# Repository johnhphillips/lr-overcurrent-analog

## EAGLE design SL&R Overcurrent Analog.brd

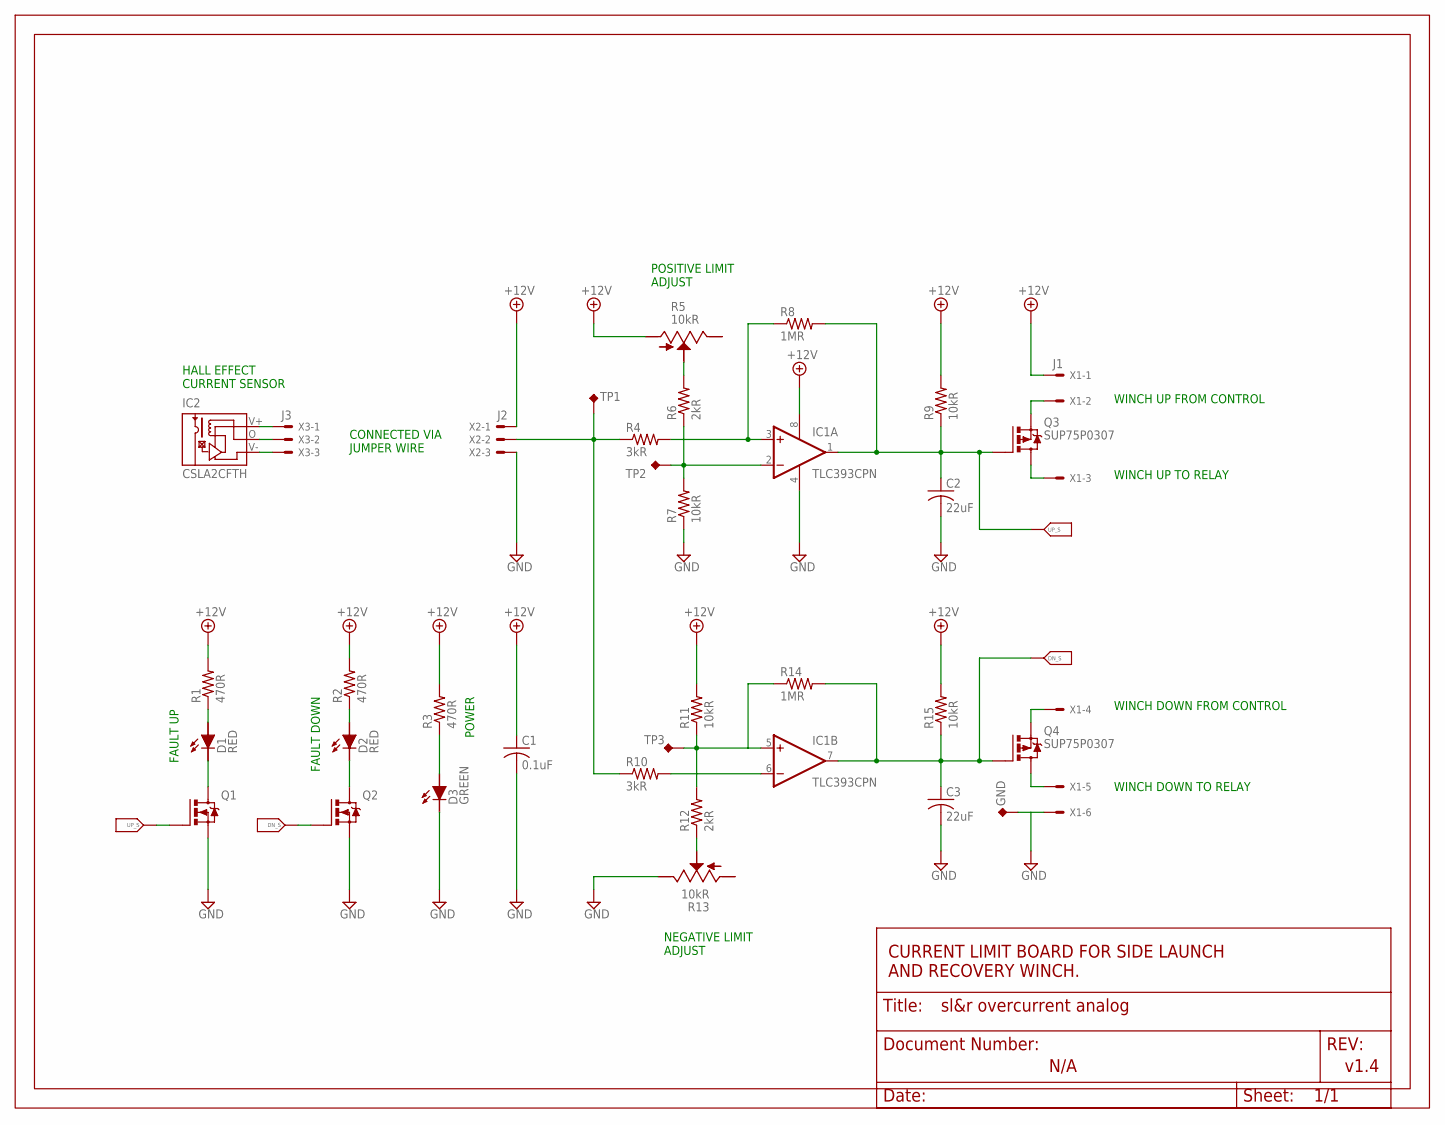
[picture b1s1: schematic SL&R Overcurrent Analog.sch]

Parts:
C1: 0.1uF; C050-024X044
C2, C3: 22uF; C025-050X050
D1, D2: RED; LED5MM
D3: GREEN; LED5MM
FRAME1: FRAME_A_L
GND: TEST_POINT; TESTLOOP
IC1: TLC393CPN; DIL08
IC2: CSLA2CFTH; CSLA2CF
Q1, Q2: 2N7000; TO92-
Q3, Q4: SUP75P0307; TO220BV
R1, R2, R3: 470R; 0204/7
R4, R10: 3kR; 0204/7
R5, R13: 10kR; RTRIM3296W
R6, R12: 2kR; 0204/7
R7, R9, R11, R15: 10kR; 0204/7
R8, R14: 1MR; 0204/7
TP1, TP2, TP3: TEST_POINT; TESTLOOP
U$1: DOCFIELD
X1: J1; 22-23-2061
X2: J2; 22-23-2031
X3: J3; 22-23-2031

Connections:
+12V: C1.1, IC1.8 (V+), R1.2, R2.2, R3.2, R5.3, R9.2, R11.2, R15.2, X1.1, X2.1
GND: C1.2, C2.2, C3.2, D3.K (C), GND.P$1, IC1.4 (V-), Q1.3 (S), Q2.3 (S), R7.1, R13.1, X1.6, X2.3
unnamed: IC1.3 (+IN), R4.2, R8.1
unnamed: IC1.2 (-IN), R6.1, R7.2, TP2.P$1
unnamed: D1.A, R1.1
unnamed: IC1.6 (-IN), R10.2
unnamed: IC1.5 (+IN), R11.1, R12.2, R14.1, TP3.P$1
unnamed: C2.1, IC1.1 (OUT), Q1.2 (G), Q3.G, R8.2, R9.1
unnamed: C3.1, IC1.7 (OUT), Q2.2 (G), Q4.G, R14.2, R15.1
unnamed: Q3.S, X1.2
unnamed: Q3.D, X1.3
unnamed: Q4.S, X1.4
unnamed: Q4.D, X1.5
unnamed: IC2.V+, X3.1
unnamed: IC2.V-, X3.3
unnamed: IC2.O (M), X3.2
unnamed: R4.1, R10.1, TP1.P$1, X2.2
unnamed: D1.K (C), Q1.1 (D)
unnamed: D2.A, R2.1
unnamed: D2.K (C), Q2.1 (D)
unnamed: D3.A, R3.1
unnamed: R5.2, R6.2
unnamed: R12.1, R13.2

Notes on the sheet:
HALL EFFECT CURRENT SENSOR
v1.4
CURRENT LIMIT BOARD FOR SIDE LAUNCH AND RECOVERY WINCH.
CONNECTED VIA JUMPER WIRE
N/A
WINCH UP FROM CONTROL
WINCH UP TO RELAY
WINCH DOWN FROM CONTROL
WINCH DOWN TO RELAY
FAULT UP
FAULT DOWN
POWER
POSITIVE LIMIT ADJUST
NEGATIVE LIMIT ADJUST

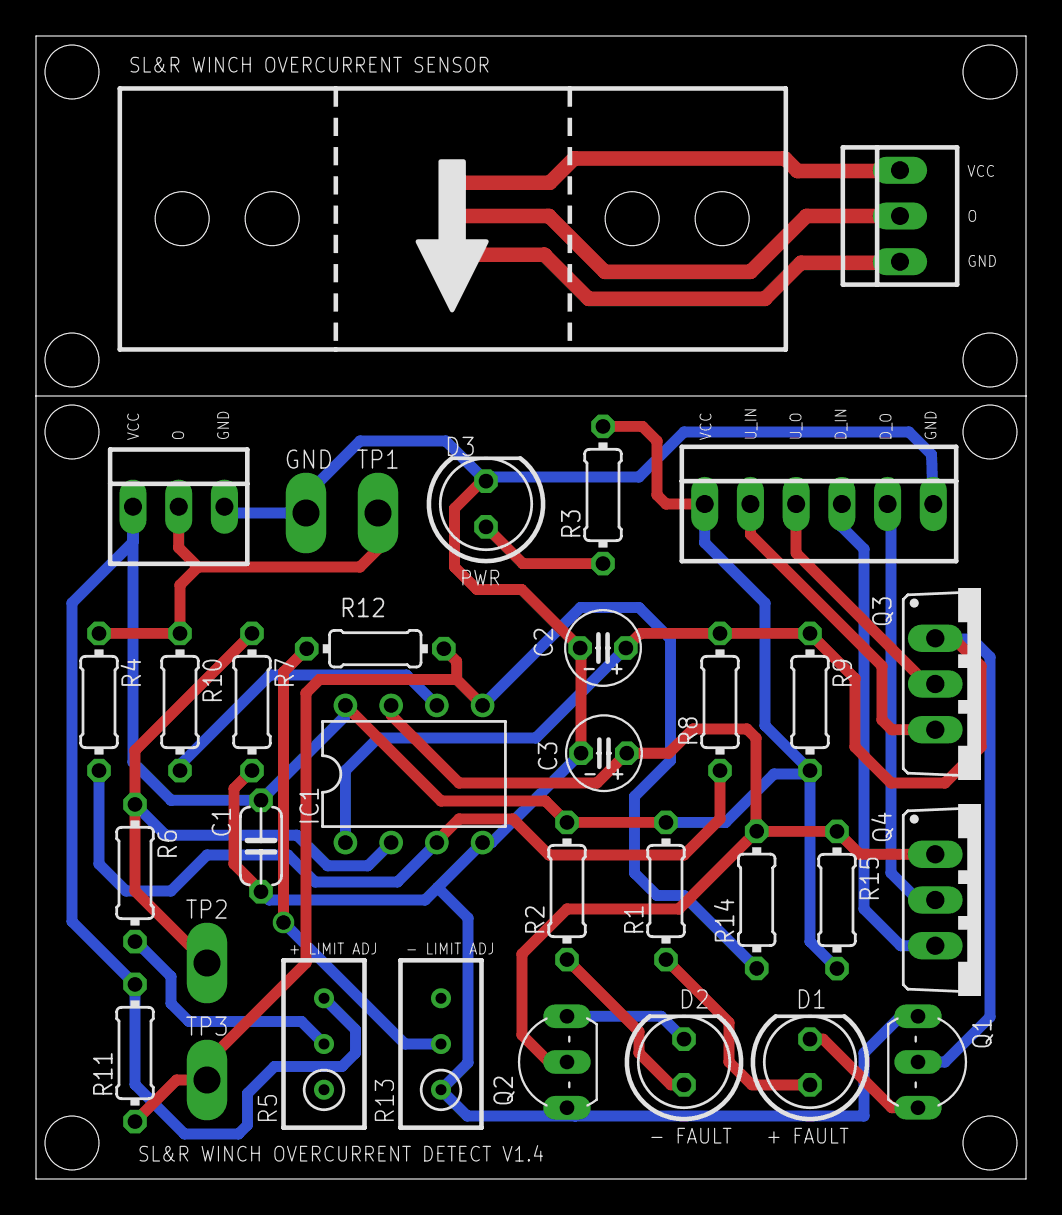
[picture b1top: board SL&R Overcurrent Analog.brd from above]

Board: 2 copper layers, 55.0 x 63.5 mm, 36 parts (0 on the bottom side), 23 nets.

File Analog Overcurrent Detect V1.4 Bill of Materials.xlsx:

Part | Device / Value | Description | Digikey P/N | Unit Cost
C1 | Capacitor, 0.1uF | Capacitor, Through-hole Ceramic | 445-5258-ND | 0.28999999999999998
C2 | Capacitor, 20uF | Capacitor, Through-hole Electrolytic | P15803CT-ND | 0.4
C3 | Capacitor, 20uF | Capacitor, Through-hole Electrolytic | P15803CT-ND | 0.4
D1 | LED | LED 5MM, Red | C5SMFRJS-CT0W0BB1-ND | 0.16
D2 | LED | LED 5MM, Red | C5SMFRJS-CT0W0BB1-ND | 0.16
D3 | LED | LED 5MM, Green | C5SMFGJS-CV0Y0792CT-ND | 0.3
IC1 | Current Transducer | DC Current Transducer, +/- 125A | 480-4824-ND | 21.95
IC2 | Comparator | Comparator, DIP Package | 296-1849-5-ND | 1.0900000000000001
Q1 | MOSFET | N-Channel Power MOSFET | 2N7000TACT-ND | 0.39
Q2 | MOSFET | N-Channel Power MOSFET | 2N7000TACT-ND | 0.39
Q3 | MOSFET | P-Channel Power MOSFET | IXTP32P05T-ND | 1.86
Q4 | MOSFET | P-Channel Power MOSFET | IXTP32P05T-ND | 1.86
R1 | Resistor, 470R | Resistor, Through-hole 0.5W | S470HCT-ND | 3.2399999999999998E-2
R2 | Resistor, 470R | Resistor, Through-hole 0.5W | S470HCT-ND | 3.2399999999999998E-2
R3 | Resistor, 470R | Resistor, Through-hole 0.5W | S470HCT-ND | 3.2399999999999998E-2
R4 | Resistor, 3kR | Resistor, Through-hole 0.25W | 3.0KQBK-ND | 0.1
R5 | Resistor, 10kR Trimmer | Resistor, Through-hole 0.5W | 3386P-103LF-ND | 1.53
R6 | Resistor, 2kR | Resistor, Through-hole 0.25W | 2.0KQBK-ND | 0.1
R7 | Resistor, 10kR | Resistor, Through-hole 0.25W | 10KQBK-ND | 0.1
R8 | Resistor, 1MR | Resistor, Through-hole 0.25W | 1.0MQBK-ND | 0.1
R9 | Resistor, 10kR | Resistor, Through-hole 0.25W | 10KQBK-ND | 0.1
R10 | Resistor, 3kR | Resistor, Through-hole 0.25W | 3.0KQBK-ND | 0.1
R11 | Resistor, 10kR | Resistor, Through-hole 0.25W | 10KQBK-ND | 0.1
R12 | Resistor, 2kR | Resistor, Through-hole 0.25W | 2.0KQBK-ND | 0.1
R13 | Resistor, 10kR Trimmer | Resistor, Through-hole 0.5W | 3386P-103LF-ND | 1.53
R14 | Resistor, 1MR | Resistor, Through-hole 0.25W | 1.0MQBK-ND | 0.1
R15 | Resistor, 10kR | Resistor, Through-hole 0.25W | 10KQBK-ND | 0.1
TP1 | Test Point | Terminal Test Point 0.5" x 0.15" | 1046K-ND | 0.23
TP2 | Test Point | Terminal Test Point 0.5" x 0.15" | 1046K-ND | 0.23
TP3 | Test Point | Terminal Test Point 0.5" x 0.15" | 1046K-ND | 0.23
GND | Test Point | Terminal Test Point 0.5" x 0.15" | 1046K-ND | 0.23
 |  |  | Total: | 33.637200000000007

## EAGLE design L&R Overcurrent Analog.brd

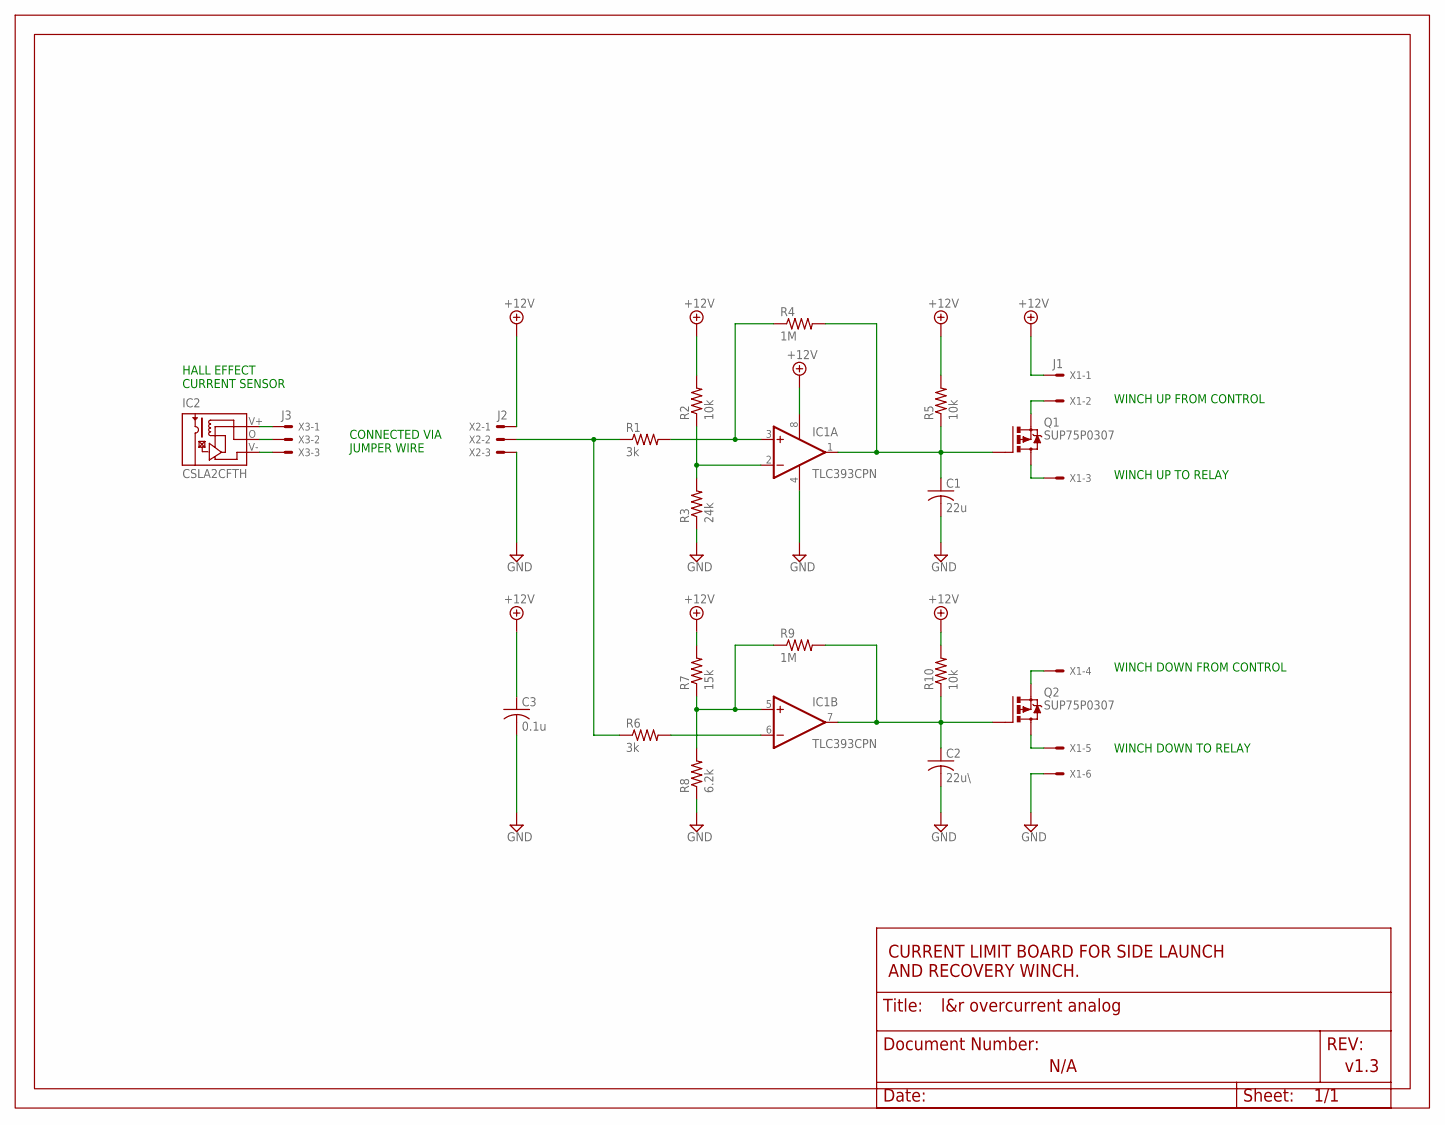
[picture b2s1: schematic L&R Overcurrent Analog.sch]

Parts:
C1: 22u; C025-050X050
C2: 22u\; C025-050X050
C3: 0.1u; C050-024X044
FRAME1: FRAME_A_L
IC1: TLC393CPN; DIL08
IC2: CSLA2CFTH; CSLA2CF
Q1, Q2: SUP75P0307; TO220BV
R1, R6: 3k; 0204/7
R2, R5, R10: 10k; 0204/7
R3: 24k; 0204/7
R4, R9: 1M; 0204/7
R7: 15k; 0204/7
R8: 6.2k; 0204/7
U$1: DOCFIELD
X1: J1; 22-23-2061
X2: J2; 22-23-2031
X3: J3; 22-23-2031

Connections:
+12V: C3.1, IC1.8 (V+), R2.2, R5.2, R7.2, R10.2, X1.1, X2.1
GND: C1.2, C2.2, C3.2, IC1.4 (V-), R3.1, R8.1, X1.6, X2.3
unnamed: IC1.3 (+IN), R1.2, R4.1
unnamed: IC1.2 (-IN), R2.1, R3.2
unnamed: IC1.6 (-IN), R6.2
unnamed: IC1.5 (+IN), R7.1, R8.2, R9.1
unnamed: C1.1, IC1.1 (OUT), Q1.G, R4.2, R5.1
unnamed: C2.1, IC1.7 (OUT), Q2.G, R9.2, R10.1
unnamed: Q1.S, X1.2
unnamed: Q1.D, X1.3
unnamed: Q2.S, X1.4
unnamed: Q2.D, X1.5
unnamed: IC2.V+, X3.1
unnamed: IC2.V-, X3.3
unnamed: IC2.O (M), X3.2
unnamed: R1.1, R6.1, X2.2

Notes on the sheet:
HALL EFFECT CURRENT SENSOR
v1.3
CURRENT LIMIT BOARD FOR SIDE LAUNCH AND RECOVERY WINCH.
CONNECTED VIA JUMPER WIRE
N/A
WINCH UP FROM CONTROL
WINCH UP TO RELAY
WINCH DOWN FROM CONTROL
WINCH DOWN TO RELAY

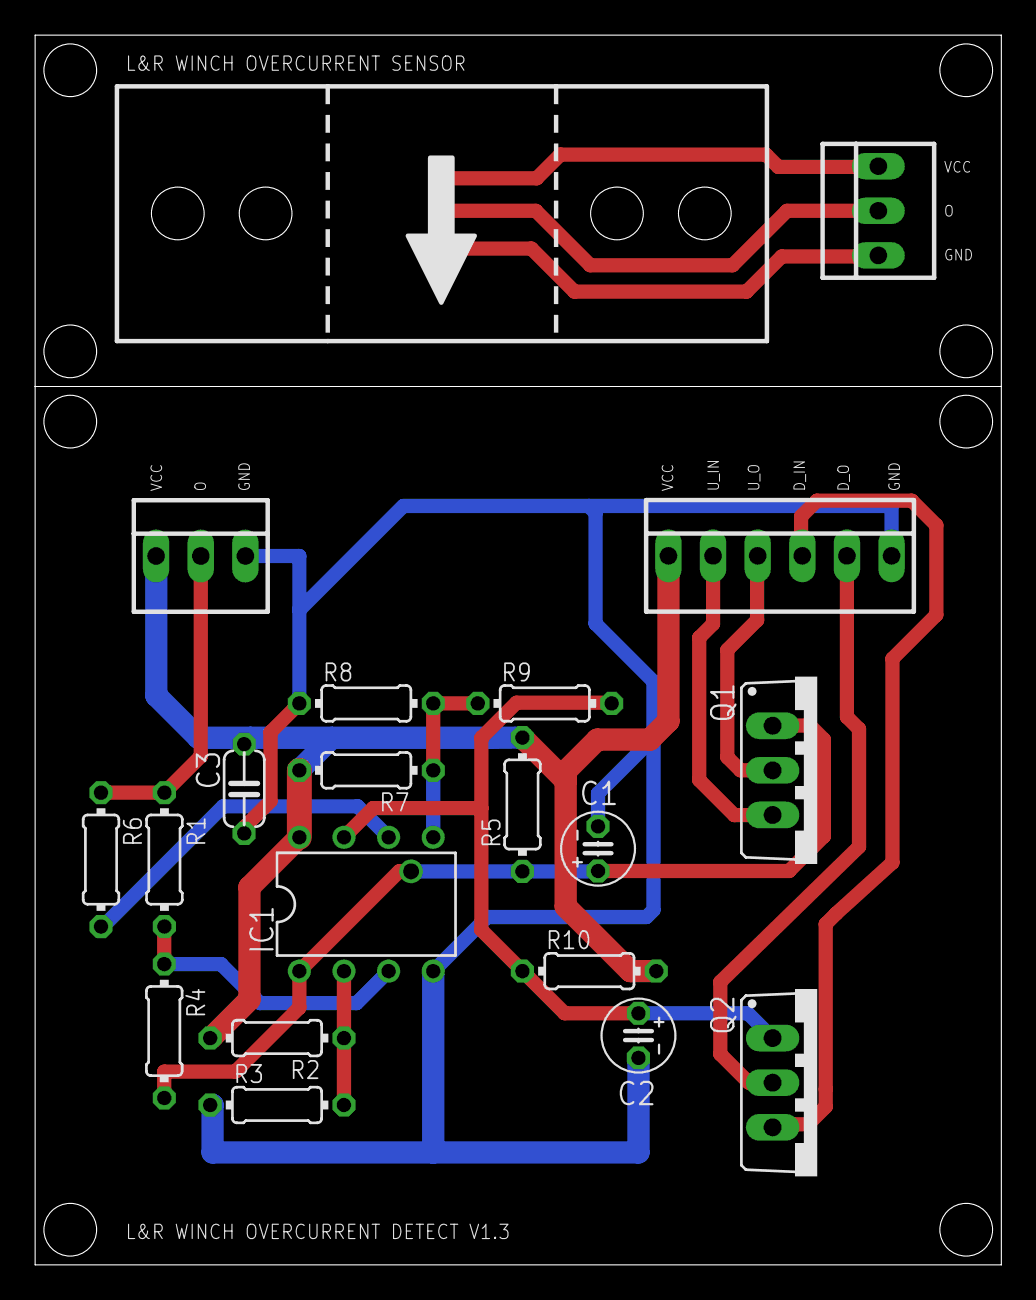
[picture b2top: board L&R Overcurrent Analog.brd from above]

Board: 2 copper layers, 55.0 x 70.0 mm, 22 parts (0 on the bottom side), 16 nets.

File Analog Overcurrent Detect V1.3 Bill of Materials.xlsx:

Part | Device / Value | Description | Part Number | Digikey P/N | Unit Cost
C1 | Capacitor, 20uF | Capacitor, Through-hole Electrolytic | EEA-GA1E220H | P15803CT-ND | 0.4
C2 | Capacitor, 20uF | Capacitor, Through-hole Electrolytic | EEA-GA1E220H | P15803CT-ND | 0.4
C3 | Capacitor, 0.1uF | Capacitor, Through-hole Ceramic | FK28X7R1H104K | 445-5258-ND | 0.28999999999999998
IC1 | Current Transducer | DC Current Transducer, +/- 125A | CSLA2CF | 480-4824-ND | 21.95
IC2 | Comparator | Comparator, DIP Package | TLC393CP | 296-1849-5-ND | 1.0900000000000001
Q1 | MOSFET | P-Channel Power MOSFET | SUP75P03-07-E3 | SUP75P03-07-E3-ND | 2.9
Q2 | MOSFET | P-Channel Power MOSFET | SUP75P03-07-E3 | SUP75P03-07-E3-ND | 2.9
R1 | Resistor, 3k | Resistor, Through-hole 0.25W | CFR-25JB-523K | 3.0KQBK-ND | 0.1
R2 | Resistor, 10k | Resistor, Through-hole 0.25W | CFR-25JB-5210K | 10KQBK-ND | 0.1
R3 | Resistor, 24k | Resistor, Through-hole 0.25W | CFR-25JR-5224K | 24KQTR-ND | 0.1
R4 | Resistor, 1M | Resistor, Through-hole 0.25W | CFR-25JB-521M | 1.0MQBK-ND | 0.1
R5 | Resistor, 10k | Resistor, Through-hole 0.25W | CFR-25JB-5210K | 10KQBK-ND | 0.1
R6 | Resistor, 3k | Resistor, Through-hole 0.25W | CFR-25JB-523K | 3.0KQBK-ND | 0.1
R7 | Resistor, 15k | Resistor, Through-hole 0.25W | CFR-25JB-5215K | 15KQBK-ND | 0.1
R8 | Resistor, 6.2k | Resistor, Through-hole 0.25W | CFR-25JB-526K2 | 6.2KQBK-ND | 0.1
R9 | Resistor, 1M | Resistor, Through-hole 0.25W | CFR-25JB-521M | 1.0MQBK-ND | 0.1
R10 | Resistor, 10k | Resistor, Through-hole 0.25W | CFR-25JB-5210K | 10KQBK-ND | 0.1
 |  |  |  | Total: | 30.93000000000001

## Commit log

2013-09-03 Moved current transducer closer on board, larger ground pour.
2013-09-03 Added IC filter cap, changed RC timer caps to electrolytic.
2013-09-03 Added stand off holes to board, increased board size.
2013-09-03 Changed to 5V, added regulator. PCB not done.
2013-09-03 Split transducer from main board, added schematic frame.
2013-09-04 Added .gitignore and .gitattributes
2014-03-28 Updated / added document frames and added cutout to PCB
2014-03-28 Minor updates to silkscreen, added cutout to PCB
2014-05-12 Updated board dimensions, added BOM
2014-05-12 BOM Formatting
2014-05-20 Indicators, adjustable limits, test points
2014-05-21 Minor updates
